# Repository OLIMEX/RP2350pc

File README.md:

# RP2350pc
RP2350 all in one computer with 16MB Flash, 8MB PSRAM,  4 USB host, DVI/HDMI output, Stereo Audio codec and amplifier the ultimate RISC-V and Retro computer emulator

https://www.olimex.com/Products/RaspberryPi/PICO/RP2350pc/

## Licensee
* Hardware is released under CERN Open Hardware Licence Version 2 - Strongly Reciprocal
* Documentation is released under CC BY-SA 4.0

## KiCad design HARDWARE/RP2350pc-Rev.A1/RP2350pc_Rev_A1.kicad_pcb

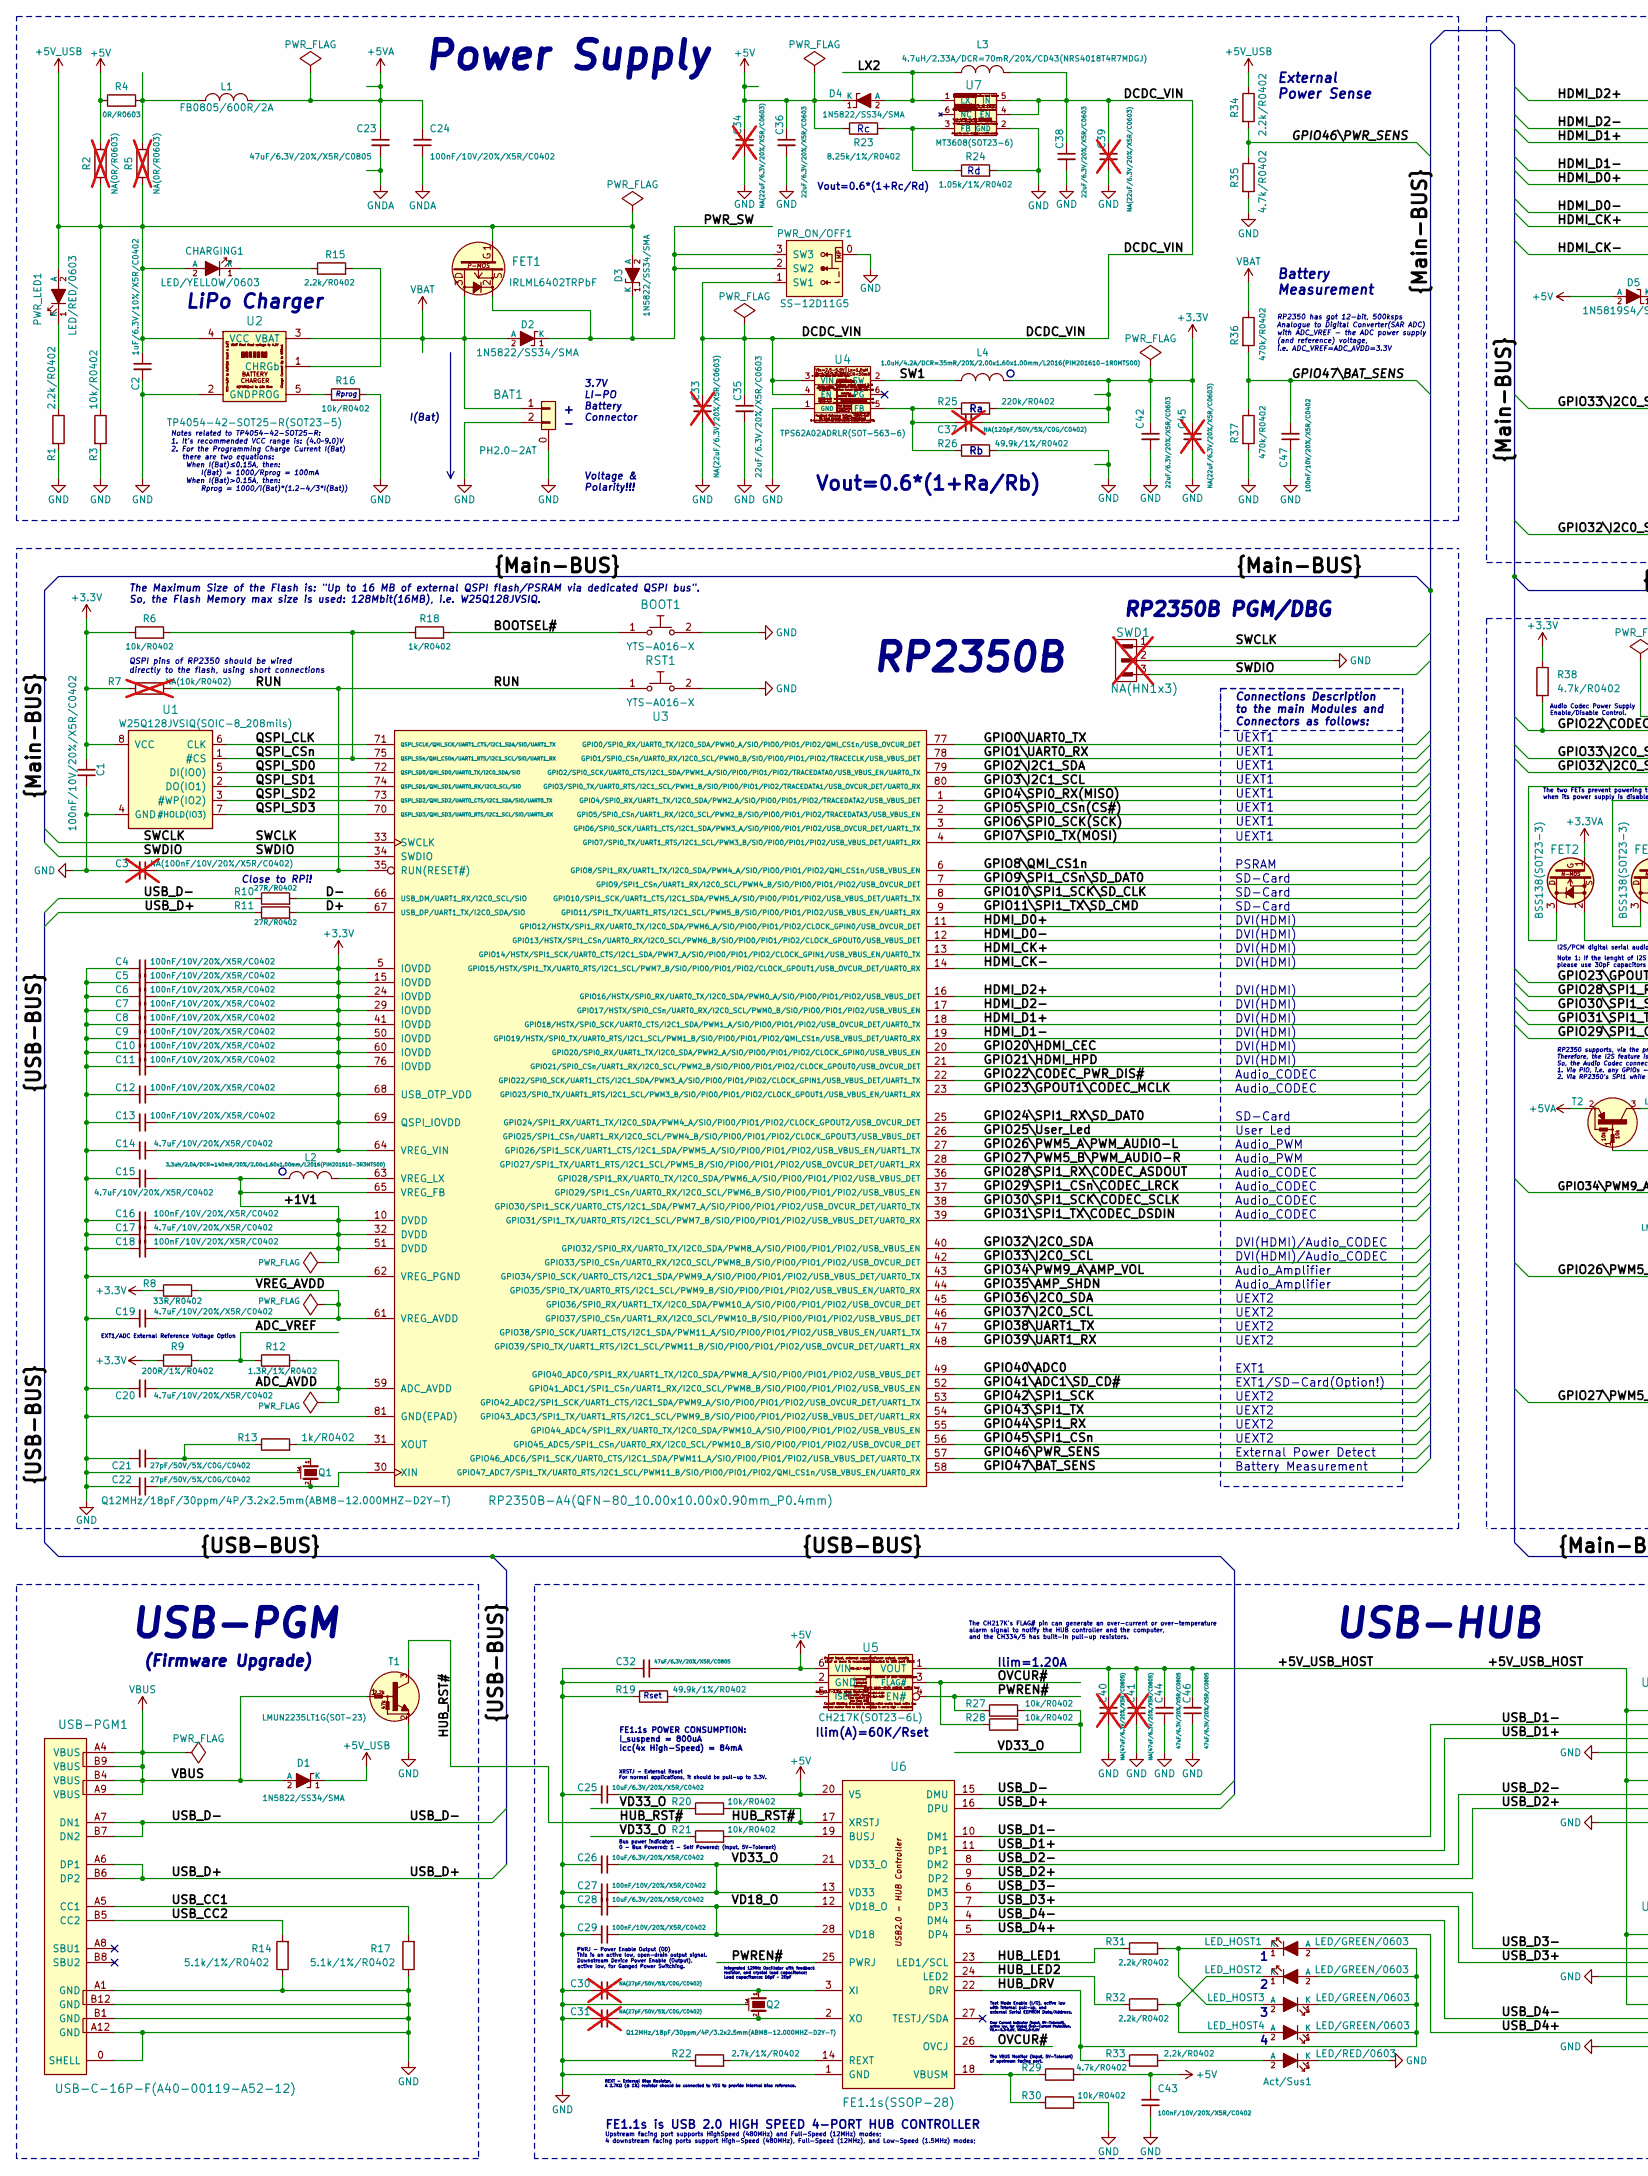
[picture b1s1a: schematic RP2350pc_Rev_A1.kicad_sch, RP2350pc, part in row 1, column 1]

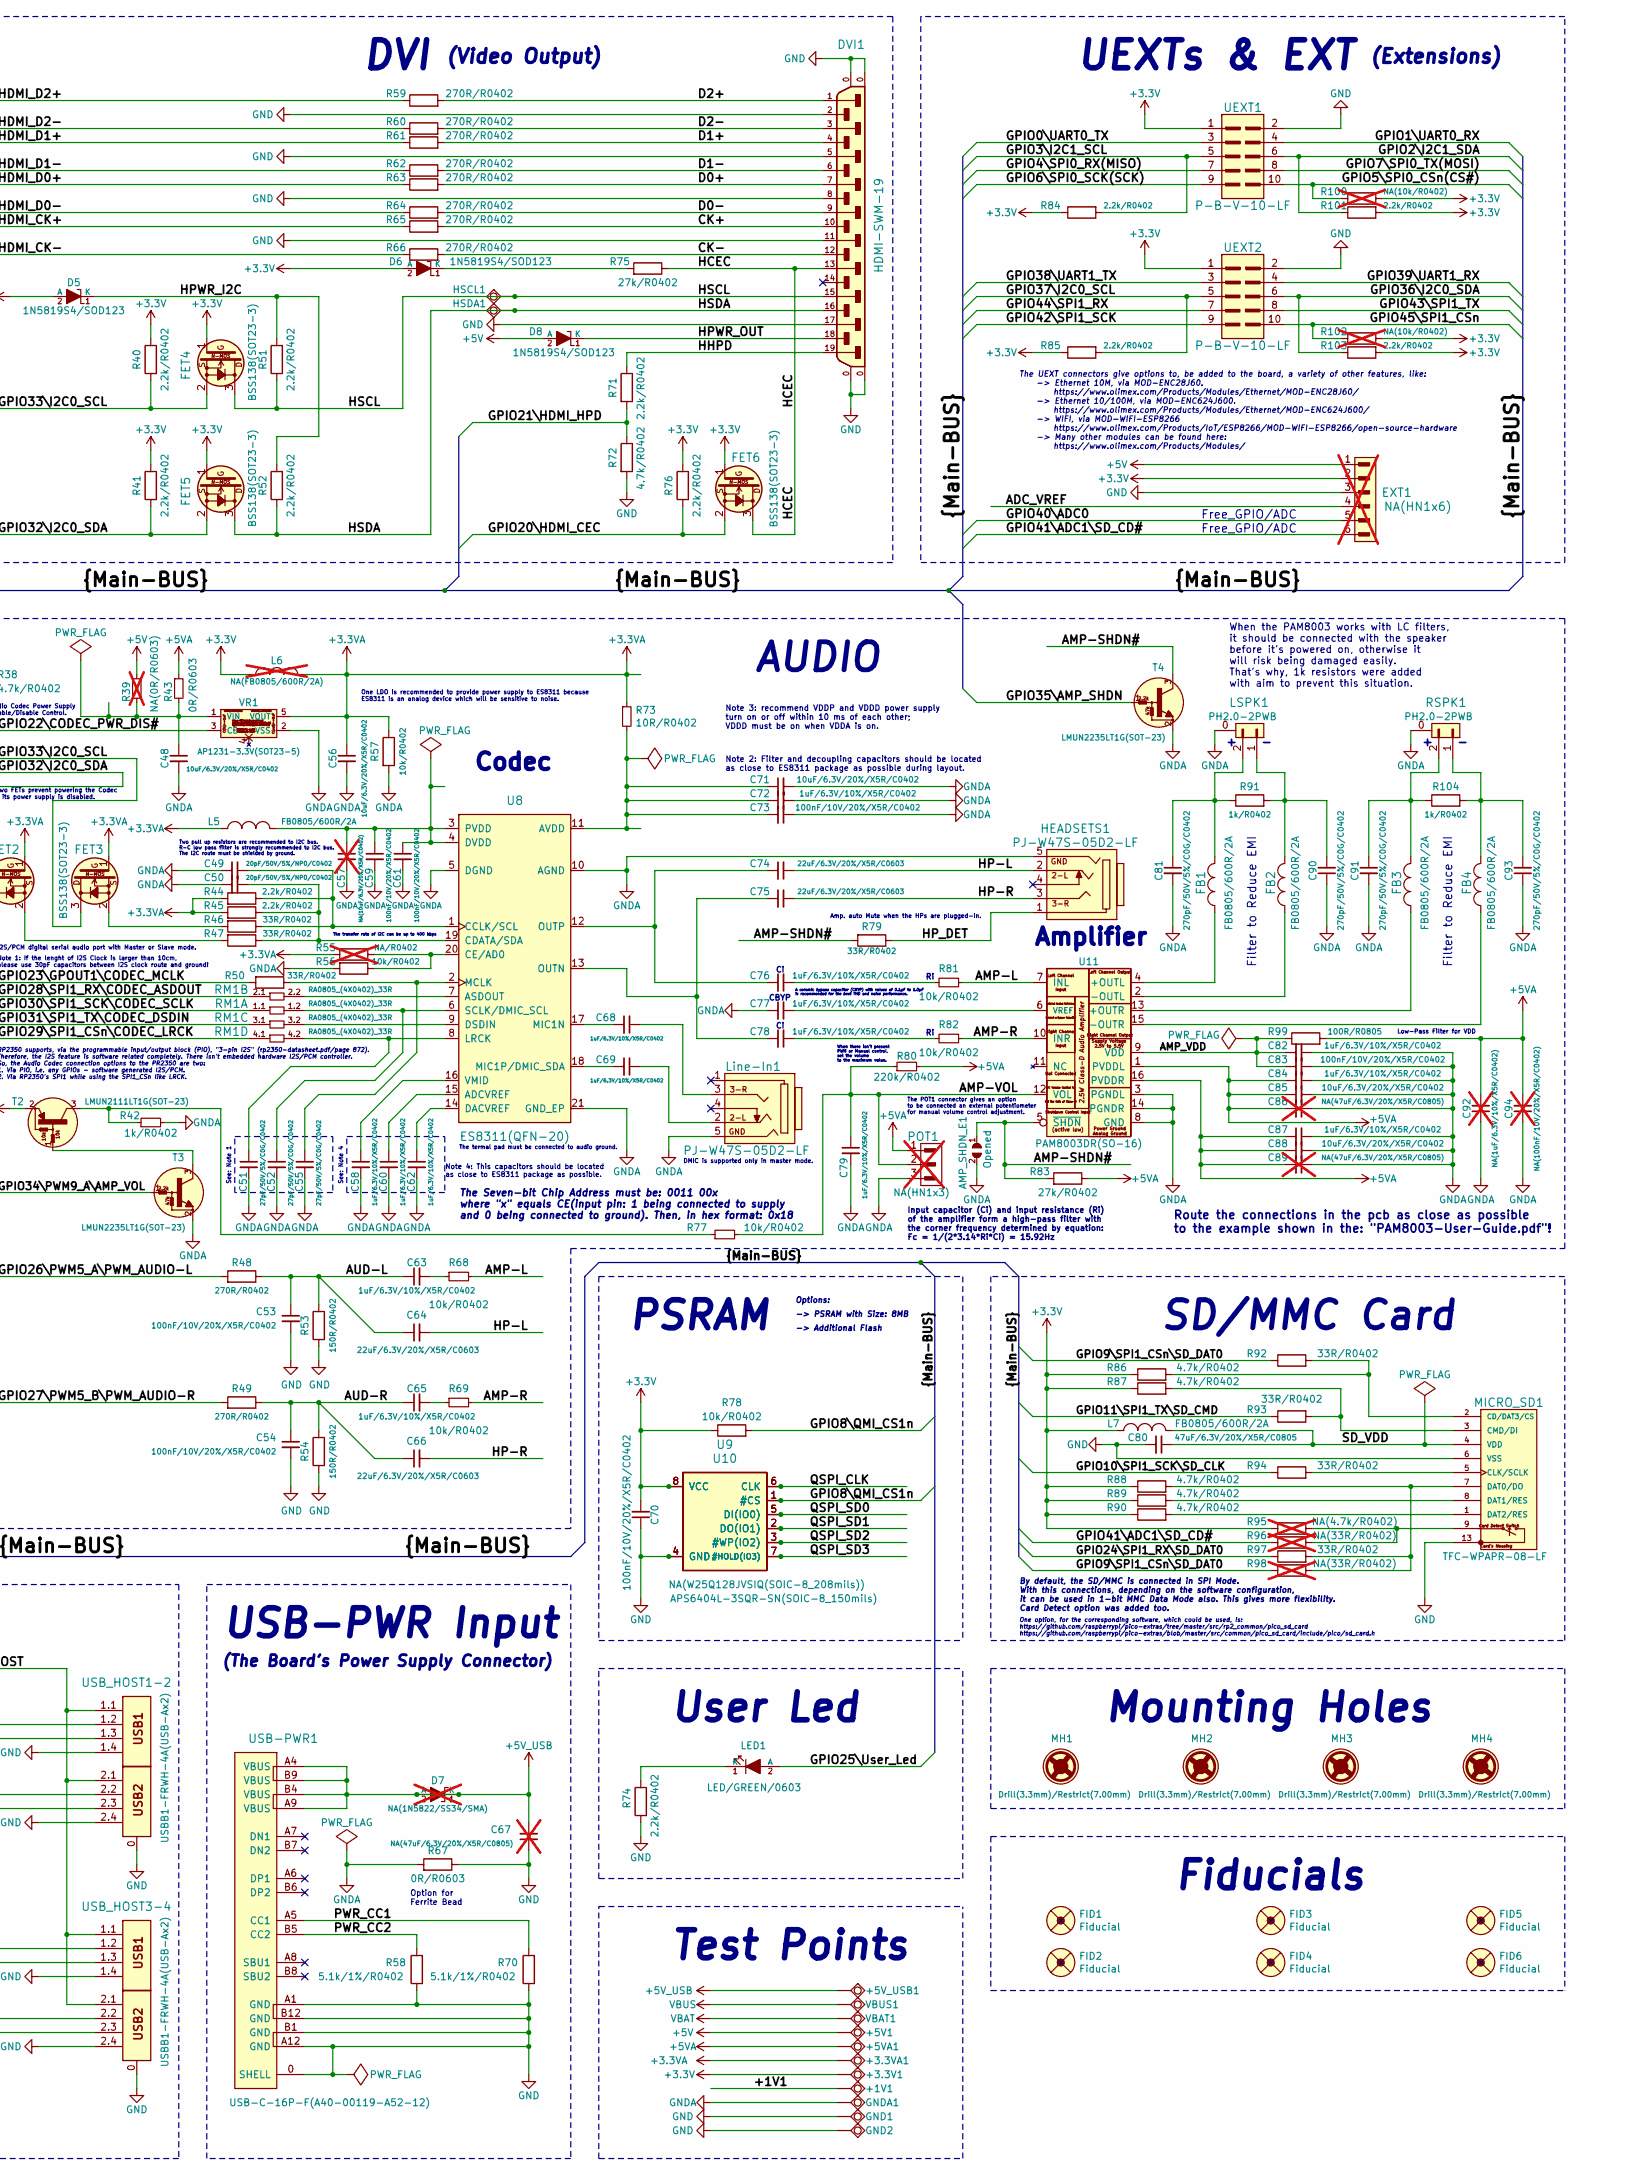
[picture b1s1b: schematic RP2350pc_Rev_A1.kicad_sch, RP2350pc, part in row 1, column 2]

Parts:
+1V1, +3.3V1, +3.3VA1, +5V1, +5VA1, +5V_USB1: TESTPAD; TESTPAD_40-ROUND
AMP_SHDN_E1: Opened; SJ
Act/Sus1: LED/RED/0603; LED_0603_KA
BAT1: PH2.0-2AT; PH2.0-2AT(BAT)
BOOT1: YTS-A016-X
C1, C4, C5, C6, C7, C8, C9, C10, C11, C12, C13, C16, C18, C24, C27, C29, C43, C47, C53, C54, C59, C61, C70, C73, C83: 100nF/10V/20%/X5R/C0402; C_0402_5MIL_DWS
C2, C58, C60, C62, C63, C65, C68, C69, C72, C76, C77, C78, C79, C82, C84, C87: 1uF/6.3V/10%/X5R/C0402; C_0402_5MIL_DWS
C3, C94: NA(100nF/10V/20%/X5R/C0402); C_0402_5MIL_DWS; not fitted
C14, C15, C17, C19, C20: 4.7uF/10V/20%/X5R/C0402; C_0402_5MIL_DWS
C21, C22, C51, C52, C55: 27pF/50V/5%/C0G/C0402; C_0402_5MIL_DWS
C23, C32, C44, C46, C80: 47uF/6.3V/20%/X5R/C0805; C_0805_5MIL_DWS
C25, C26, C28, C48, C56, C71, C85, C88: 10uF/6.3V/20%/X5R/C0402; C_0402_5MIL_DWS
C30, C31: NA(27pF/50V/5%/C0G/C0402); C_0402_5MIL_DWS; not fitted
C33, C34, C39, C45: NA(22uF/6.3V/20%/X5R/C0603); C_0603_5MIL_DWS; not fitted
C35, C36, C38, C42, C64, C66, C74, C75: 22uF/6.3V/20%/X5R/C0603; C_0603_5MIL_DWS
C37: NA(120pF/50V/5%/C0G/C0402); C_0402_5MIL_DWS; not fitted
C40, C41, C67, C86, C89: NA(47uF/6.3V/20%/X5R/C0805); C_0805_5MIL_DWS; not fitted
C49, C50: 20pF/50V/5%/NP0/C0402; C_0402_5MIL_DWS
C57: NA(10uF/6.3V/20%/X5R/C0402); C_0402_5MIL_DWS; not fitted
C81, C90, C91, C93: 270pF/50V/5%/C0G/C0402; C_0402_5MIL_DWS
C92: NA(1uF/6.3V/10%/X5R/C0402); C_0402_5MIL_DWS; not fitted
CHARGING1: LED/YELLOW/0603; LED_0603_KA
D1, D2, D3, D4: 1N5822/SS34/SMA; SMA-KA
D5, D6, D8: 1N5819S4/SOD123; SOD-123_1C-2A_KA
D7: NA(1N5822/SS34/SMA); SMA-KA; not fitted
DVI1: HDMI-SWM-19; HDMI-SWM-19_Paste
EXT1: NA(HN1x6); HN1x6; not fitted
FB1, FB2, FB3, FB4: FB0805/600R/2A; L_0805_5MIL_DWS
FET1: IRLML6402TRPbF; SOT23
FET2, FET3, FET4, FET5, FET6: BSS138(SOT23-3); SOT23
FID1, FID2, FID3: Fiducial; Fiducial1x3_Paste
FID4, FID5, FID6: Fiducial; Fiducial1x3
GND1: TESTPAD; TEST_PAD40x70_SQUARE
GND2: TESTPAD; TESTPAD_40-ROUND
GNDA1: TESTPAD; TESTPAD_40-ROUND
HEADSETS1: PJ-W47S-05D2-LF; PJ-W47S-05D2-LF_5PIN_V2_LongerPads
HSCL1: TESTPAD; TESTPAD_40-ROUND
HSDA1: TESTPAD; TESTPAD_40-ROUND
L1, L5, L7: FB0805/600R/2A; L_0805_5MIL_DWS
L2: 3.3uH/2.0A/DCR=140mR/20%/2.00x1.60x1.00mm/L2016(P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; L_2016_MM
L3: 4.7uH/2.33A/DCR=70mR/20%/CD43(NRS4018T4R7MDGJ); CD42(43)
L4: 1.0uH/4.2A/DCR=35mR/20%/2.00x1.60x1.00mm/L2016(PI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; L_2016_MM
L6: NA(FB0805/600R/2A); L_0805_5MIL_DWS; not fitted
LED1: LED/GREEN/0603; LED_0603_KA
LED_HOST1, LED_HOST2, LED_HOST3, LED_HOST4: LED/GREEN/0603; LED_0603_KA
LSPK1: PH2.0-2PWB
Line-In1: PJ-W47S-05D2-LF; PJ-W47S-05D2-LF_5PIN_V2_LongerPads
MH1, MH2, MH3, MH4: Drill(3.3mm)/Restrict(7.00mm); Mounting_Hole_Drill-3.3mm_Clerance-7mm
MICRO_SD1: TFC-WPAPR-08-LF; TFC-WPAPR-08
POT1: NA(HN1x3); HN1x3; not fitted
PWR_LED1: LED/RED/0603; LED_0603_KA
PWR_ON/OFF1: SS-12D11G5
Q1, Q2: Q12MHz/18pF/30ppm/4P/3.2x2.5mm(ABM8-12.000MHZ-D2Y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; TSX-3.2x2.5mm_GND(3)
R1, R15, R31, R32, R33, R34, R40, R41, R44, R45, R51, R52, R71, R74, R76, R84, R85, R101, R103: 2.2k/R0402; R_0402_5MIL_DWS
R2, R5, R39: NA(0R/R0603); R_0603_5MIL_DWS; not fitted
R3, R6, R16, R20, R21, R27, R28, R30, R56, R57, R68, R69, R77, R78, R81, R82: 10k/R0402; R_0402_5MIL_DWS
R4, R43, R67: 0R/R0603; R_0603_5MIL_DWS
R7, R100, R102: NA(10k/R0402); R_0402_5MIL_DWS; not fitted
R8, R46, R47, R50, R79, R92, R93, R94, R97: 33R/R0402; R_0402_5MIL_DWS
R9: 200R/1%/R0402; R_0402_5MIL_DWS
R10, R11: 27R/R0402; R_0402_5MIL_DWS
R12: 1.3R/1%/R0402; R_0402_5MIL_DWS
R13, R18, R42, R91, R104: 1k/R0402; R_0402_5MIL_DWS
R14, R17, R58, R70: 5.1k/1%/R0402; R_0402_5MIL_DWS
R19, R26: 49.9k/1%/R0402; R_0402_5MIL_DWS
R22: 2.7k/1%/R0402; R_0402_5MIL_DWS
R23: 8.25k/1%/R0402; R_0402_5MIL_DWS
R24: 1.05k/1%/R0402; R_0402_5MIL_DWS
R25, R80: 220k/R0402; R_0402_5MIL_DWS
R29, R35, R38, R72, R86, R87, R88, R89, R90: 4.7k/R0402; R_0402_5MIL_DWS
R36, R37: 470k/R0402; R_0402_5MIL_DWS
R48, R49, R59, R60, R61, R62, R63, R64, R65, R66: 270R/R0402; R_0402_5MIL_DWS
R53, R54: 150R/R0402; R_0402_5MIL_DWS
R55: NA/R0402; R_0402_5MIL_DWS; not fitted
R73: 10R/R0402; R_0402_5MIL_DWS
R75, R83: 27k/R0402; R_0402_5MIL_DWS
R95: NA(4.7k/R0402); R_0402_5MIL_DWS; not fitted
R96, R98: NA(33R/R0402); R_0402_5MIL_DWS; not fitted
R99: 100R/R0805; R_0805_5MIL_DWS
RM1: RA0805_(4X0402)_33R; RA0805_(4X0402)_xx_BIGGEROUTPADS
RSPK1: PH2.0-2PWB
RST1: YTS-A016-X
SWD1: NA(HN1x3); HN1x3; not fitted
T1, T3, T4: LMUN2235LT1G(SOT-23); SOT23
T2: LMUN2111LT1G(SOT-23); SOT23
U1: W25Q128JVSIQ(SOIC-8_208mils); SO-8_208mil
U2: TP4054-42-SOT25-R(SOT23-5); SOT-23-5
U3: RP2350B-A4(QFN-80_10.00x10.00x0.90mm_P0.4mm); QFN-80_10.00x10.00x0.90mm_P0.4mm
U4: TPS62A02ADRLR(SOT-563-6); SOT-563-6
U5: CH217K(SOT23-6L); SOT23-6
U6: FE1.1s(SSOP-28); SSOP28_10x4mm_Pitch_0.64mm
U7: MT3608(SOT23-6); SOT23-6
U8: ES8311(QFN-20); QFN-20_EP(21)_3x3x0.6mm_Pitch_0.4mm
U9: NA(W25Q128JVSIQ(SOIC-8_208mils)); SO-8_208mil
U10: APS6404L-3SQR-SN(SOIC-8_150mils); SO-8
U11: PAM8003DR(SO-16); SO-16
UEXT1, UEXT2: P-B-V-10-LF; GBH-254-SMT-10
USB-PGM1: USB-C-16P-F(A40-00119-A52-12); USB2.0_TYPE-C(A40-00119-A52-12)_Paste
USB-PWR1: USB-C-16P-F(A40-00119-A52-12); USB2.0_TYPE-C(A40-00119-A52-12)_Paste
USB_HOST1-2, USB_HOST3-4: USBB1-FRWH-4A(USB-Ax2); USB_TWO_LEVEL
VBAT1: TESTPAD; TESTPAD_40-ROUND
VBUS1: TESTPAD; TESTPAD_40-ROUND
VR1: AP1231-3.3V(SOT23-5); SOT-23-5

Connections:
+3.3V: +3.3V1.1 (Pad), C1.2, C4.1, C5.1, C6.1, C7.1, C8.1, C9.1, C10.1, C11.1, C12.1, C13.1, C14.1, C37.2, C42.1, C45.1, C70.2, D6.2 (A), EXT1.2, FET4.1 (G), FET5.1 (G), FET6.1 (G), L4.1, L6.1, L7.1, R6.1, R7.1, R8.1, R9.1, R25.2, R38.1, R40.1, R41.1, R76.1, R78.1, R84.1, R85.1, R86.1, R87.1, R88.1, R89.1, R90.1, R95.1, R100.2, R101.2, R102.2, R103.2, U1.8 (VCC), U3.5 (IOVDD), U3.15 (IOVDD), U3.24 (IOVDD), U3.29 (IOVDD), U3.41 (IOVDD), U3.50 (IOVDD), U3.60 (IOVDD), U3.64 (VREG_VIN), U3.68 (USB_OTP_VDD), U3.69 (QSPI_IOVDD), U3.76 (IOVDD), U9.8 (VCC), U10.8 (VCC), UEXT1.1, UEXT2.1
+3.3VA: +3.3VA1.1 (Pad), C56.1, FET2.1 (G), FET3.1 (G), L5.1, L6.2, R44.2, R45.2, R55.2, R57.1, R73.1, VR1.5 (VOUT)
+5V: +5V1.1 (Pad), C25.1, C32.1, C34.1, C36.1, C43.2, D4.1 (K), D5.2 (A), D8.2 (A), EXT1.1, R2.2, R4.1, R23.1, R29.2, R39.1, U5.6 (VIN), U6.20 (V5)
+5VA: +5VA1.1 (Pad), C23.1, C24.2, C84.2, C85.1, C86.2, C87.2, C88.1, C89.2, C92.2, C94.2, L1.2, POT1.1, R43.1, R80.2, R83.1, R99.2, T2.2 (E), U11.1 (PVDDL), U11.16 (PVDDR)
+5V_USB: +5V_USB1.1 (Pad), C2.1, C67.2, CHARGING1.2 (A), D1.1 (K), D3.2 (A), D7.1 (K), D7.2 (A), FET1.1, PWR_LED1.2 (A), R2.1, R3.1, R5.1, R34.1, U2.4 (VCC), USB-PWR1.A4 (VBUS), USB-PWR1.A9 (VBUS), USB-PWR1.B4 (VBUS), USB-PWR1.B9 (VBUS)
/+1V1: +1V1.1 (Pad), C15.1, C16.1, C17.1, C18.1, L2.1, U3.10 (DVDD), U3.32 (DVDD), U3.51 (DVDD), U3.65 (VREG_FB)
/+5V_USB_HOST: C40.2, C41.2, C44.2, C46.2, U5.1 (VOUT), USB_HOST1-2.1.1, USB_HOST1-2.2.1, USB_HOST3-4.1.1, USB_HOST3-4.2.1
/ADC_AVDD: C20.1, R12.2, U3.59 (ADC_AVDD)
/ADC_VREF: EXT1.4, R9.2, R12.1
/AMP-L: R68.2, R81.1, U11.7 (INL)
/AMP-R: R69.2, R82.1, U11.10 (INR)
/AMP-SHDN#: AMP_SHDN_E1.1, R79.2, R83.2, T4.3 (C), U11.5 (~SHDN)
/AMP-VOL: C79.1, POT1.2, R77.2, R80.1, U11.12 (VOL)
/AMP_VDD: C82.2, C83.2, R99.1, U11.9 (VDD)
/AUD-L: C53.1, C63.1, C64.1, R48.1, R53.1
/AUD-R: C54.1, C65.1, C66.1, R49.1, R54.1
/BOOTSEL#: BOOT1.1, R18.2
/CK+: DVI1.10, R65.2
/CK-: DVI1.12, R66.2
/D0+: DVI1.7, R63.2
/D0-: DVI1.9, R64.2
/D1+: DVI1.4, R61.2
/D1-: DVI1.6, R62.2
/D2+: DVI1.1, R59.2
/D2-: DVI1.3, R60.2
/D+: R11.2, U3.67 (USB_DP/UART1_TX/I2C0_SDA/SIO)
/D-: R10.2, U3.66 (USB_DM/UART1_RX/I2C0_SCL/SIO)
/DCDC_VIN: C33.1, C35.1, C38.1, C39.1, L3.2, PWR_ON/OFF1.1 (SW1), U4.3 (VIN), U4.4 (EN), U7.4 (EN), U7.5 (IN)
/GPIO0\UART0_TX: U3.77 (GPIO0/SPI0_RX/UART0_TX/I2C0_SDA/PWM0_A/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), UEXT1.3
/GPIO1\UART0_RX: U3.78 (GPIO1/SPI0_CSn/UART0_RX/I2C0_SCL/PWM0_B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), UEXT1.4
/GPIO2\I2C1_SDA: R101.1, U3.79 (GPIO2/SPI0_SCK/UART0_CTS/I2C1_SDA/PWM1_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), UEXT1.6
/GPIO3\I2C1_SCL: R84.2, U3.80 (GPIO3/SPI0_TX/UART0_RTS/I2C1_SCL/PWM1_B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), UEXT1.5
/GPIO4\SPI0_RX(MISO): U3.1 (GPIO4/SPI0_RX/UART1_TX/I2C0_SDA/PWM2_A/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), UEXT1.7
/GPIO5\SPI0_CSn(CS#): R100.1, U3.2 (GPIO5/SPI0_CSn/UART1_RX/I2C0_SCL/PWM2_B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), UEXT1.10
/GPIO6\SPI0_SCK(SCK): U3.3 (GPIO6/SPI0_SCK/UART1_CTS/I2C1_SDA/PWM3_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), UEXT1.9
/GPIO7\SPI0_TX(MOSI): U3.4 (GPIO7/SPI0_TX/UART1_RTS/I2C1_SCL/PWM3_B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), UEXT1.8
/GPIO8\QMI_CS1n: R78.2, U3.6 (GPIO8/SPI1_RX/UART1_TX/I2C0_SDA/PWM4_A/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), U9.1 (#CS), U10.1 (#CS)
/GPIO9\SPI1_CSn\SD_DAT0: R92.1, R98.1, U3.7 (GPIO9/SPI1_CSn/UART1_RX/I2C0_SCL/PWM4_B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)
/GPIO10\SPI1_SCK\SD_CLK: R94.1, U3.8 (GPIO10/SPI1_SCK/UART1_CTS/I2C1_SDA/PWM5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)
/GPIO11\SPI1_TX\SD_CMD: R93.1, U3.9 (GPIO11/SPI1_TX/UART1_RTS/I2C1_SCL/PWM5_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)
/GPIO20\HDMI_CEC: FET6.2 (S), R76.2, U3.20 (GPIO20/SPI0_RX/UART1_TX/I2C0_SDA/PWM2_A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)
/GPIO21\HDMI_HPD: R71.2, R72.1, U3.21 (GPIO21/SPI0_CSn/UART1_RX/I2C0_SCL/PWM2_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)
/GPIO22\CODEC_PWR_DIS#: R38.2, U3.22 (GPIO22/SPI0_SCK/UART1_CTS/I2C1_SDA/PWM3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), VR1.3 (CE)
/GPIO23\GPOUT1\CODEC_MCLK: R50.2, U3.23 (GPIO23/SPI0_TX/UART1_RTS/I2C1_SCL/PWM3_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)
/GPIO24\SPI1_RX\SD_DAT0: R97.1, U3.25 (GPIO24/SPI1_RX/UART1_TX/I2C0_SDA/PWM4_A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)
/GPIO25\User_Led: LED1.2 (A), U3.26 (GPIO25/SPI1_CSn/UART1_RX/I2C0_SCL/PWM4_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)
/GPIO26\PWM5_A\PWM_AUDIO-L: R48.2, U3.27 (GPIO26/SPI1_SCK/UART1_CTS/I2C1_SDA/PWM5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)
/GPIO27\PWM5_B\PWM_AUDIO-R: R49.2, U3.28 (GPIO27/SPI1_TX/UART1_RTS/I2C1_SCL/PWM5_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)
/GPIO28\SPI1_RX\CODEC_ASDOUT: RM1.2.1, U3.36 (GPIO28/SPI1_RX/UART0_TX/I2C0_SDA/PWM6_A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)
/GPIO29\SPI1_CSn\CODEC_LRCK: RM1.4.1, U3.37 (GPIO29/SPI1_CSn/UART0_RX/I2C0_SCL/PWM6_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)
/GPIO30\SPI1_SCK\CODEC_SCLK: RM1.1.1, U3.38 (GPIO30/SPI1_SCK/UART0_CTS/I2C1_SDA/PWM7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)
/GPIO31\SPI1_TX\CODEC_DSDIN: RM1.3.1, U3.39 (GPIO31/SPI1_TX/UART0_RTS/I2C1_SCL/PWM7_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)
/GPIO32\I2C0_SDA: FET2.3 (D), FET5.2 (S), R41.2, U3.40 (GPIO32/SPI0_RX/UART0_TX/I2C0_SDA/PWM8_A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)
/GPIO33\I2C0_SCL: FET3.3 (D), FET4.2 (S), R40.2, U3.42 (GPIO33/SPI0_CSn/UART0_RX/I2C0_SCL/PWM8_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)
/GPIO34\PWM9_A\AMP_VOL: T3.1 (B), U3.43 (GPIO34/SPI0_SCK/UART0_CTS/I2C1_SDA/PWM9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)
/GPIO35\AMP_SHDN: T4.1 (B), U3.44 (GPIO35/SPI0_TX/UART0_RTS/I2C1_SCL/PWM9_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)
/GPIO36\I2C0_SDA: R103.1, U3.45 (GPIO36/SPI0_RX/UART1_TX/I2C0_SDA/PWM10_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), UEXT2.6
/GPIO37\I2C0_SCL: R85.2, U3.46 (GPIO37/SPI0_CSn/UART1_RX/I2C0_SCL/PWM10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), UEXT2.5
/GPIO38\UART1_TX: U3.47 (GPIO38/SPI0_SCK/UART1_CTS/I2C1_SDA/PWM1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), UEXT2.3
/GPIO39\UART1_RX: U3.48 (GPIO39/SPI0_TX/UART1_RTS/I2C1_SCL/PWM11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), UEXT2.4
/GPIO40\ADC0: EXT1.5, U3.49 (GPIO40_ADC0/SPI1_RX/UART1_TX/I2C0_SDA/P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)
/GPIO41\ADC1\SD_CD#: EXT1.6, R96.1, U3.52 (GPIO41_ADC1/SPI1_CSn/UART1_RX/I2C0_SCL/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)
/GPIO42\SPI1_SCK: U3.53 (GPIO42_ADC2/SPI1_SCK/UART1_CTS/I2C1_SDA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), UEXT2.9
/GPIO43\SPI1_TX: U3.54 (GPIO43_ADC3/SPI1_TX/UART1_RTS/I2C1_SCL/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), UEXT2.8
/GPIO44\SPI1_RX: U3.55 (GPIO44_ADC4/SPI1_RX/UART0_TX/I2C0_SDA/P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), UEXT2.7
/GPIO45\SPI1_CSn: R102.1, U3.56 (GPIO45_ADC5/SPI1_CSn/UART0_RX/I2C0_SCL/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), UEXT2.10
/GPIO46\PWR_SENS: R34.2, R35.1, U3.57 (GPIO46_ADC6/SPI1_SCK/UART0_CTS/I2C1_SDA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)
/GPIO47\BAT_SENS: C47.2, R36.2, R37.1, U3.58 (GPIO47_ADC7/SPI1_TX/UART0_RTS/I2C1_SCL/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)
/HCEC: DVI1.13, FET6.3 (D), R75.1
/HDMI_CK+: R65.1, U3.13 (GPIO14/HSTX/SPI1_SCK/UART0_CTS/I2C1_SDA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)
/HDMI_CK-: R66.1, U3.14 (GPIO15/HSTX/SPI1_TX/UART0_RTS/I2C1_SCL/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)
/HDMI_D0+: R63.1, U3.11 (GPIO12/HSTX/SPI1_RX/UART0_TX/I2C0_SDA/P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)
/HDMI_D0-: R64.1, U3.12 (GPIO13/HSTX/SPI1_CSn/UART0_RX/I2C0_SCL/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)
/HDMI_D1+: R61.1, U3.18 (GPIO18/HSTX/SPI0_SCK/UART0_CTS/I2C1_SDA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)
/HDMI_D1-: R62.1, U3.19 (GPIO19/HSTX/SPI0_TX/UART0_RTS/I2C1_SCL/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)
/HDMI_D2+: R59.1, U3.16 (GPIO16/HSTX/SPI0_RX/UART0_TX/I2C0_SDA/P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)
/HDMI_D2-: R60.1, U3.17 (GPIO17/HSTX/SPI0_CSn/UART0_RX/I2C0_SCL/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)
/HHPD: DVI1.19, R71.1
/HP-L: C64.2, C74.1, HEADSETS1.2
/HP-R: C66.2, C75.1, HEADSETS1.3
/HPWR_I2C: D5.1 (K), R51.2, R52.2
/HPWR_OUT: D8.1 (K), DVI1.18
/HP_DET: HEADSETS1.1, R79.1
/HSCL: DVI1.15, FET4.3 (D), HSCL1.1 (Pad), R51.1
/HSDA: DVI1.16, FET5.3 (D), HSDA1.1 (Pad), R52.1
/HUB_DRV: LED_HOST1.2 (A), LED_HOST2.2 (A), LED_HOST3.1 (K), LED_HOST4.1 (K), R33.1, U6.22 (DRV)
/HUB_LED1: R31.1, U6.23 (LED1/SCL)
/HUB_LED2: R32.1, U6.24 (LED2)
/HUB_RST#: R20.2, T1.3 (C), U6.17 (XRSTJ)
/LX2: D4.2 (A), L3.1, U7.1 (LX)
/OVCUR#: R28.1, U5.3 (FLAG#), U6.26 (OVCJ)
/PWREN#: R27.1, U5.4 (EN#), U6.25 (PWRJ)
/PWR_CC1: R70.2, USB-PWR1.A5 (CC1)
/PWR_CC2: R58.2, USB-PWR1.B5 (CC2)
/PWR_SW: D2.1 (K), D3.1 (K), FET1.2, PWR_ON/OFF1.2 (SW2), PWR_ON/OFF1.3 (SW3)
/QSPI_CLK: U1.6 (CLK), U3.71 (QSPI_SCLK/QMI_SCK/UART1_CTS/I2C1_SDA/SI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), U9.6 (CLK), U10.6 (CLK)
/QSPI_CSn: R6.2, R18.1, U1.1 (#CS), U3.75 (QSPI_SSn/QMI_CS0n/UART1_RTS/I2C1_SCL/SI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)
/QSPI_SD0: U1.5 (DI(IO0)), U3.72 (QSPI_SD0/QMI_SD0/UART0_TX/I2C0_SDA/SIO), U9.5 (DI(IO0)), U10.5 (DI(IO0))
/QSPI_SD1: U1.2 (DO(IO1)), U3.74 (QSPI_SD1/QMI_SD1/UART0_RX/I2C0_SCL/SIO), U9.2 (DO(IO1)), U10.2 (DO(IO1))
/QSPI_SD2: U1.3 (#WP(IO2)), U3.73 (QSPI_SD2/QMI_SD2/UART0_CTS/I2C1_SDA/SIO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), U9.3 (#WP(IO2)), U10.3 (#WP(IO2))
/QSPI_SD3: U1.7 (#HOLD(IO3)), U3.70 (QSPI_SD3/QMI_SD3/UART0_RTS/I2C1_SCL/SIO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), U9.7 (#HOLD(IO3)), U10.7 (#HOLD(IO3))
/RUN: C3.1, R7.2, RST1.1, U3.35 (RUN(RESET#))
/SD_VDD: C80.1, L7.2, MICRO_SD1.4 (VDD)
/SW1: L4.2, U4.2 (SW)
/SWCLK: SWD1.1, U3.33 (SWCLK)
/SWDIO: SWD1.3, U3.34 (SWDIO)
/USB_CC1: R17.2, USB-PGM1.A5 (CC1)
/USB_CC2: R14.2, USB-PGM1.B5 (CC2)
/USB_D1+: U6.11 (DP1), USB_HOST1-2.1.3
/USB_D1-: U6.10 (DM1), USB_HOST1-2.1.2
/USB_D2+: U6.9 (DP2), USB_HOST1-2.2.3
/USB_D2-: U6.8 (DM2), USB_HOST1-2.2.2
/USB_D3+: U6.7 (DP3), USB_HOST3-4.1.3
/USB_D3-: U6.6 (DM3), USB_HOST3-4.1.2
/USB_D4+: U6.5 (DP4), USB_HOST3-4.2.3
/USB_D4-: U6.4 (DM4), USB_HOST3-4.2.2
/USB_D+: R11.1, U6.16 (DPU), USB-PGM1.A6 (DP1), USB-PGM1.B6 (DP2)
/USB_D-: R10.1, U6.15 (DMU), USB-PGM1.A7 (DN1), USB-PGM1.B7 (DN2)
/VD18_O: C28.1, C29.1, U6.12 (VD18_O), U6.28 (VD18)
/VD33_O: C26.1, C27.1, R20.1, R21.1, R27.2, R28.2, U6.13 (VD33), U6.21 (VD33_O)
/VREG_AVDD: C19.1, R8.2, U3.61 (VREG_AVDD)
GND: Act/Sus1.1 (K), BAT1.0, BAT1.2, BOOT1.2, C1.1, C2.2, C3.2, C4.2, C5.2, C6.2, C7.2, C8.2, C9.2, C10.2, C11.2, C12.2, C13.2, C14.2, C15.2, C16.2, C17.2, C18.2, C19.2, C20.2, C21.2, C22.2, C25.2, C26.2, C27.2, C28.2, C29.2, C30.2, C31.2, C32.2, C33.2, C34.2, C35.2, C36.2, C38.2, C39.2, C40.1, C41.1, C42.2, C43.1, C44.1, C45.2, C46.1, C47.1, C53.2, C54.2, C67.1, C70.1, C80.2, DVI1.0 (23), DVI1.2, DVI1.5, DVI1.8, DVI1.11, DVI1.17, EXT1.3, GND1.1 (Pad), GND2.1 (Pad), MICRO_SD1.6 (VSS), MICRO_SD1.10, MICRO_SD1.11, MICRO_SD1.12, MICRO_SD1.13, PWR_ON/OFF1.0, Q1.3 (case), Q2.3 (case), R1.2, R3.2, R14.1, R16.2, R17.1, R19.1, R22.1, R24.2, R26.2, R30.2, R35.2, R37.2, R53.2, R54.2, R58.1, R67.1, R70.1, R72.2, R74.2, RST1.2, SWD1.2, T1.2 (E), U1.4 (GND), U2.2 (GND), U3.62 (VREG_PGND), U3.81 (GND(EPAD)), U4.1 (GND), U5.2 (GND), U6.1 (GND), U7.2 (GND), U9.4 (GND), U10.4 (GND), UEXT1.2, UEXT2.2, USB-PGM1.0 (SHELL), USB-PGM1.A1 (GND), USB-PGM1.A12 (GND), USB-PGM1.B1 (GND), USB-PGM1.B12 (GND), USB-PWR1.0 (SHELL), USB-PWR1.A1 (GND), USB-PWR1.A12 (GND), USB-PWR1.B1 (GND), USB-PWR1.B12 (GND), USB_HOST1-2.0, USB_HOST1-2.1.4, USB_HOST1-2.2.4, USB_HOST3-4.0, USB_HOST3-4.1.4, USB_HOST3-4.2.4
GNDA: AMP_SHDN_E1.2, C23.2, C24.1, C48.2, C49.2, C50.2, C51.2, C52.2, C55.2, C56.2, C57.2, C58.2, C59.2, C60.2, C61.2, C62.2, C71.2, C72.2, C73.1, C77.2, C79.2, C81.2, C82.1, C83.1, C84.1, C85.2, C86.1, C87.1, C88.2, C89.1, C90.1, C91.2, C92.1, C93.1, C94.1, GNDA1.1 (Pad), HEADSETS1.5, LSPK1.0, Line-In1.5, POT1.3, R42.2, R56.2, R57.2, R67.2, RSPK1.0, T3.2 (E), T4.2 (E), U8.5 (DGND), U8.10 (AGND), U8.21 (GND_EP), U11.3 (PGNDL), U11.8 (GND), U11.14 (PGNDR), VR1.2 (VSS)
unnamed: Act/Sus1.2 (A), R33.2
unnamed: C21.1, Q1.1, R13.1
unnamed: C63.2, R68.1
unnamed: C65.2, R69.1
unnamed: C68.1, Line-In1.3
unnamed: C69.1, Line-In1.2
unnamed: C76.1, R81.2
unnamed: C78.1, R82.2
unnamed: CHARGING1.1 (K), R15.1
unnamed: D6.1 (K), R75.2
unnamed: FET2.2 (S), R47.2
unnamed: FET3.2 (S), R46.2
unnamed: L1.1, R4.2, R5.2
unnamed: LED1.1 (K), R74.1
unnamed: LED_HOST1.1 (K), LED_HOST3.2 (A), R31.2
unnamed: LED_HOST2.1 (K), LED_HOST4.2 (A), R32.2
unnamed: C90.2, FB2.1, LSPK1.1, R91.2
unnamed: C81.1, FB1.1, LSPK1.2, R91.1
unnamed: MICRO_SD1.2 (CD/DAT3/CS), R86.2, R92.2
unnamed: MICRO_SD1.5 (CLK/SCLK), R94.2
unnamed: MICRO_SD1.3 (CMD/DI), R87.2, R93.2
unnamed: MICRO_SD1.7 (DAT0/DO), R88.2, R97.2, R98.2
unnamed: MICRO_SD1.8 (DAT1/RES), R89.2
unnamed: MICRO_SD1.1 (DAT2/RES), R90.2
unnamed: MICRO_SD1.9, R95.2, R96.2
unnamed: PWR_LED1.1 (K), R1.1
unnamed: C93.2, FB4.1, R104.2, RSPK1.1
unnamed: C91.1, FB3.1, R104.1, RSPK1.2
unnamed: T2.1 (B), T3.3 (C)
unnamed: R42.1, R77.1, T2.3 (C)
unnamed: R15.2, U2.1 (CHRGb)
unnamed: R16.1, U2.5 (PROG)
unnamed: L2.2, U3.63 (VREG_LX)
unnamed: C22.1, Q1.2, U3.30 (XIN)
unnamed: R13.2, U3.31 (XOUT)
unnamed: C37.1, R25.1, R26.1, U4.5 (FB)
unnamed: R19.2, U5.5 (ISET)
unnamed: R21.2, U6.19 (BUSJ)
unnamed: R22.2, U6.14 (REXT)
unnamed: R29.1, R30.1, U6.18 (VBUSM)
unnamed: C30.1, Q2.1, U6.3 (XI)
unnamed: C31.1, Q2.2, U6.2 (XO)
unnamed: R23.2, R24.1, U7.3 (FB)
unnamed: C60.1, U8.15 (ADCVREF)
unnamed: RM1.2.2, U8.7 (ASDOUT)
unnamed: C71.1, C72.1, C73.2, R73.2, U8.11 (AVDD)
unnamed: C49.1, R44.1, R46.1, U8.1 (CCLK/SCL)
unnamed: C50.1, R45.1, R47.1, U8.19 (CDATA/SDA)
unnamed: R55.1, R56.1, U8.20 (CE/AD0)
unnamed: C62.1, U8.14 (DACVREF)
unnamed: RM1.3.2, U8.9 (DSDIN)
unnamed: C57.1, C59.1, C61.1, L5.2, U8.3 (PVDD), U8.4 (DVDD)
unnamed: C51.1, RM1.4.2, U8.8 (LRCK)
unnamed: C55.1, R50.1, U8.2 (MCLK)
unnamed: C68.2, U8.17 (MIC1N)
unnamed: C69.2, U8.18 (MIC1P/DMIC_SDA)
unnamed: C75.2, C78.2, U8.13 (OUTN)
unnamed: C74.2, C76.2, U8.12 (OUTP)
unnamed: C52.1, RM1.1.2, U8.6 (SCLK/DMIC_SCL)
unnamed: C58.1, U8.16 (VMID)
unnamed: FB1.2, U11.4 (+OUTL)
unnamed: FB3.2, U11.13 (+OUTR)
unnamed: FB2.2, U11.2 (-OUTL)
unnamed: FB4.2, U11.15 (-OUTR)
unnamed: C77.1, U11.6 (VREF)
unnamed: C48.1, R39.2, R43.2, VR1.1 (VIN)
VBAT: BAT1.1, D2.2 (A), FET1.3, R36.1, U2.3 (VBAT), VBAT1.1 (Pad)
VBUS: D1.2 (A), T1.1 (B), USB-PGM1.A4 (VBUS), USB-PGM1.A9 (VBUS), USB-PGM1.B4 (VBUS), USB-PGM1.B9 (VBUS), VBUS1.1 (Pad)

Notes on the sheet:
Filter to Reduce EMI
UEXT1
Battery Measurement
Audio_CODEC
Bus power indicator: 0 - Bus Powered; 1 - Self Powered; (Input, 5V-Tolerant)
Battery Measurement
(Firmware Upgrade)
Vout=0.6*(1+Ra/Rb)
Ilim(A)=60K/Rset
Free_GPIO/ADC
Note 3: recommend VDDP and VDDD power supply turn on or off within 10 ms of each other; VDDD must be on when VDDA is on.
DVI(HDMI)
UEXT2
RP2350 has got 12-bit, 500ksps Analogue to Digital Converter(SAR ADC) with ADC_VREF - the ADC power supply (and reference) voltage, i.e. ADC_VREF=ADC_AVDD=3.3V
See: Note 4
QSPI pins of RP2350 should be wired directly to the flash, using short connections
When there isn't present PWM or Manual control, set the volume to the maximum value.
(Video Output)
(Extensions)
3.7V LI-PO Battery Connector
Upstream facing port supports HighSpeed (480MHz) and Full-Speed (12MHz) modes; 4 downstream facing ports support High-Speed (480MHz), Full-Speed (12MHz), and Low-Speed (1.5MHz) modes;
REXT - External Bias Resistor. A 2.7KΩ (± 1%) resistor should be connected to VSS to provide internal bias reference.
PSRAM
EXT1/ADC External Reference Voltage Option
See: Note 1
The UEXT connectors give options to, be added to the board, a variety of other features, like: -> Ethernet 10M, via MOD-ENC28J60. https://www.olimex.com/Products/Modules/Ethernet/MOD-ENC28J60/ -> Ethernet 10/100M, via MOD-ENC624J600. https://www.olimex.com/Products/Modules/Ethernet/MOD-ENC624J600/ 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
The transfer rate of I2C can be up to 400 kbps
USB-PGM
USB-HUB
The POT1 connector gives an option to be connected an external potentiometer for manual volume control adjustment.
SD-Card
The CH217K's FLAG# pin can generate an over-current or over-temperature alarm signal to notify the HUB controller and the computer, and the CH334/5 has built-in pull-up resistors.
Note 2: Filter and decoupling capacitors should be located as close to ES8311 package as possible during layout.
User Led
One LDO is recommended to provide power supply to ES8311 because ES8311 is an analog device which will be sensitive to noise.
The termal pad must be connected to audio ground.
Option for Ferrite Bead
-> Additional Flash
DVI(HDMI)/Audio_CODEC
The Seven-bit Chip Address must be: 0011 00x where "x" equals CE(input pin: 1 being connected to supply and 0 being connected to ground). Then, in hex format: 0x18

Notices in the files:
HARDWARE/RP2350pc-Rev.A1/RP2350pc_Rev_A1.kicad_pcb:
(C) 2025
